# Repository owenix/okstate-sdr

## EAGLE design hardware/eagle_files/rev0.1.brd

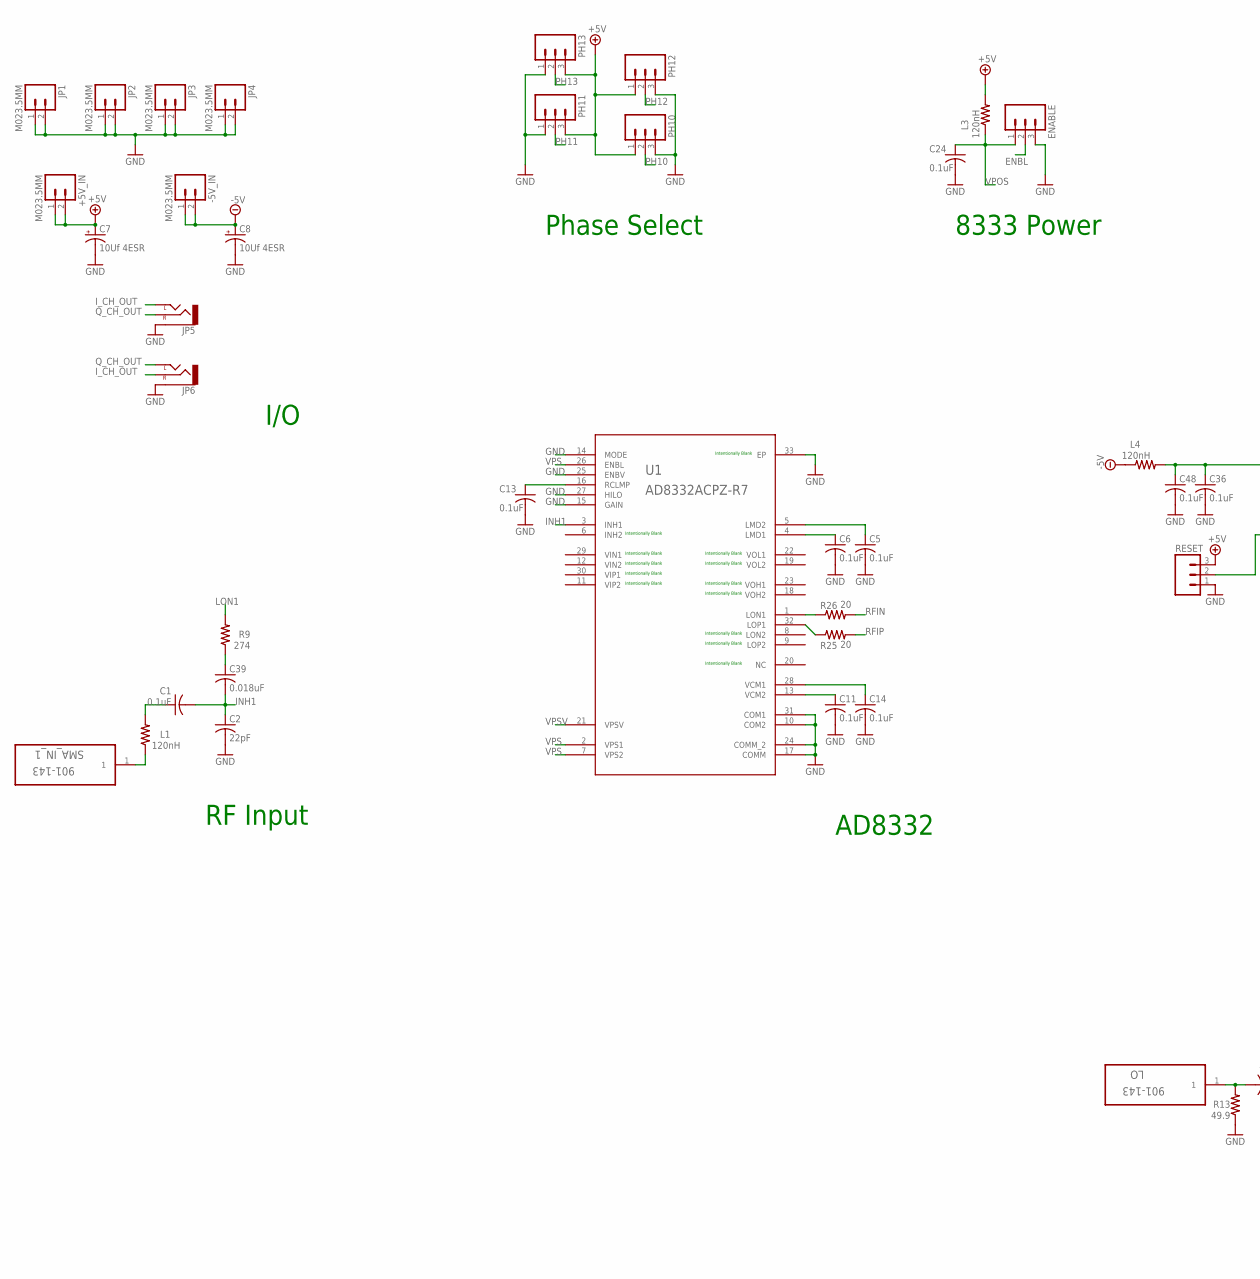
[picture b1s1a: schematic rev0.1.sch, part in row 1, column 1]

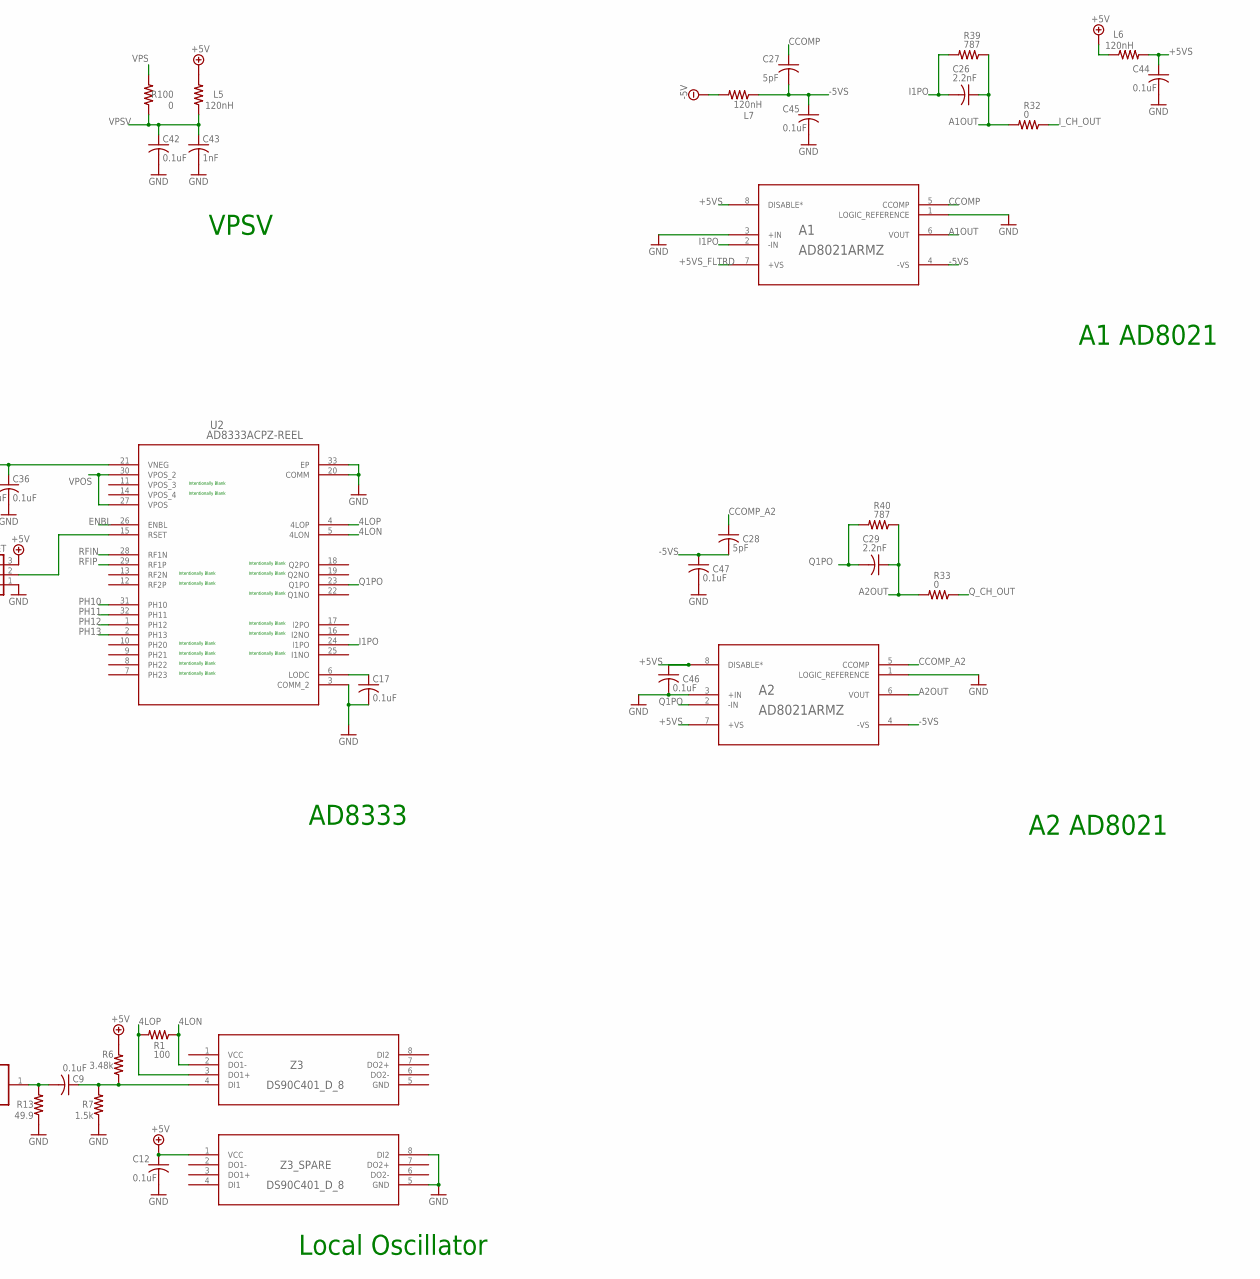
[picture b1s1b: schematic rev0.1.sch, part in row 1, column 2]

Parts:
+5V_IN: M023.5MM; SCREWTERMINAL-3.5MM-2
-5V_IN: M023.5MM; SCREWTERMINAL-3.5MM-2
A1, A2: AD8021ARMZ; RM_8
C1, C5, C6, C9, C11, C12, C13, C14, C17, C24, C36, C42, C44, C45, C46, C47, C48: 0.1uF; C1206
C2: 22pF; C1206
C7, C8: 10Uf 4ESR; CT3216
C26, C29: 2.2nF; C1206
C27, C28: 5pF; C1206
C39: 0.018uF; C1206
C43: 1nF; C1206
ENABLE: M03PTH; 1X03
JP1, JP2, JP3, JP4: M023.5MM; SCREWTERMINAL-3.5MM-2
JP5, JP6: AUDIO-JACKPTH; AUDIO-JACK
L1, L3, L4, L5, L6, L7: 120nH; R0603
LO: 901-143; AMPHENOL_901-143
PH10, PH11, PH12, PH13: M03PTH; 1X03
R1: 100; R1206
R6: 3.48k; R1206
R7: 1.5k; R1206
R9: 274; R1206
R13: 49.9; R1206
R25, R26: 20; R1206
R32, R33, R100: 0; R1206
R39, R40: 787; R1206
RESET: M03PTH; 1X03
SMA_IN_1: 901-143; AMPHENOL_901-143
U1: AD8332ACPZ-R7; CP_32_2
U2: AD8333ACPZ-REEL; CP_32_2
Z3, Z3_SPARE: DS90C401_D_8; M08A

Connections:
4LON: R1.1, U2.5 (4LON), Z3.2 (DO1-)
4LOP: R1.2, U2.4 (4LOP), Z3.3 (DO1+)
+5V: +5V_IN.1, +5V_IN.2, C7.- (+), C12.1, L3.2, L5.2, L6.1, PH10.1, PH11.3, PH12.1, PH13.3, R6.2, RESET.3, Z3_SPARE.1 (VCC)
+5VS: A1.8 (DISABLE*), A2.7 (+VS), A2.8 (DISABLE*), C44.1, C46.1, L6.2
+5VS_FLTRD: A1.7 (+VS)
-5V: -5V_IN.1, -5V_IN.2, C8.- (+), L4.1, L7.2
-5VS: A1.4 (-VS), A2.4 (-VS), C27.2, C28.2, C45.1, C47.1, L7.1
A1OUT: A1.6 (VOUT), C26.1, R32.2, R39.1
A2OUT: A2.6 (VOUT), C29.1, R33.2, R40.1
CCOMP: A1.5 (CCOMP), C27.1
CCOMP_A2: A2.5 (CCOMP), C28.1
ENBL: ENABLE.2, U2.26 (ENBL)
GND: A1.1 (LOGIC_REFERENCE), A1.3 (+IN), A2.1 (LOGIC_REFERENCE), A2.3 (+IN), C2.2, C5.2, C6.2, C7.+ (-), C8.+ (-), C11.2, C12.2, C13.2, C14.2, C17.2, C24.2, C36.2, C42.2, C43.2, C44.2, C45.2, C46.2, C47.2, C48.2, ENABLE.3, JP1.1, JP1.2, JP2.1, JP2.2, JP3.1, JP3.2, JP4.1, JP4.2, JP5.SLEEVE, JP6.SLEEVE, PH10.3, PH11.1, PH12.3, PH13.1, R7.1, R13.1, RESET.1, U1.10 (COM2), U1.14 (MODE), U1.15 (GAIN), U1.17 (COMM), U1.24 (COMM_2), U1.25 (ENBV), U1.27 (HILO), U1.31 (COM1), U1.33 (EP), U2.3 (COMM_2), U2.20 (COMM), U2.33 (EP), Z3.5 (GND), Z3_SPARE.5 (GND), Z3_SPARE.8 (DI2)
I1PO: A1.2 (-IN), C26.2, R39.2, U2.24 (I1PO)
INH1: C1.2, C2.1, C39.2, U1.3 (INH1)
I_CH_OUT: JP5.TIP (LEFT), JP6.RING (RIGHT), R32.1
LMD1: C6.1, U1.4 (LMD1)
LMD2: C5.1, U1.5 (LMD2)
LON1: R9.2, R26.1, U1.1 (LON1)
LOP1: R25.1, U1.32 (LOP1)
unnamed: C11.1, U1.13 (VCM2)
unnamed: C14.1, U1.28 (VCM1)
unnamed: C13.1, U1.16 (RCLMP)
unnamed: C1.1, L1.2
unnamed: C9.1, R6.1, R7.2, Z3.4 (DI1)
unnamed: C39.1, R9.1
unnamed: L1.1, SMA_IN_1.1
unnamed: C9.2, LO.1, R13.2
unnamed: C36.1, C48.1, L4.2, U2.21 (VNEG)
unnamed: C17.1, U2.6 (LODC)
unnamed: RESET.2, U2.15 (RSET)
PH10: PH10.2, U2.31 (PH10)
PH11: PH11.2, U2.32 (PH11)
PH12: PH12.2, U2.1 (PH12)
PH13: PH13.2, U2.2 (PH13)
Q1PO: A2.2 (-IN), C29.2, R40.2, U2.23 (Q1PO)
Q_CH_OUT: JP5.RING (RIGHT), JP6.TIP (LEFT), R33.1
RFIN: R26.2, U2.28 (RF1N)
RFIP: R25.2, U2.29 (RF1P)
VCC: Z3.1 (VCC)
VPOS: C24.1, ENABLE.1, L3.1, U2.27 (VPOS), U2.30 (VPOS_2)
VPS: R100.2, U1.2 (VPS1), U1.7 (VPS2), U1.26 (ENBL)
VPSV: C42.1, C43.1, L5.1, R100.1, U1.21 (VPSV)

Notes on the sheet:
Intentionally Blank
RF Input
VPSV
AD8332
Local Oscillator
Phase Select
8333 Power
AD8333
A1 AD8021
A2 AD8021
I/O

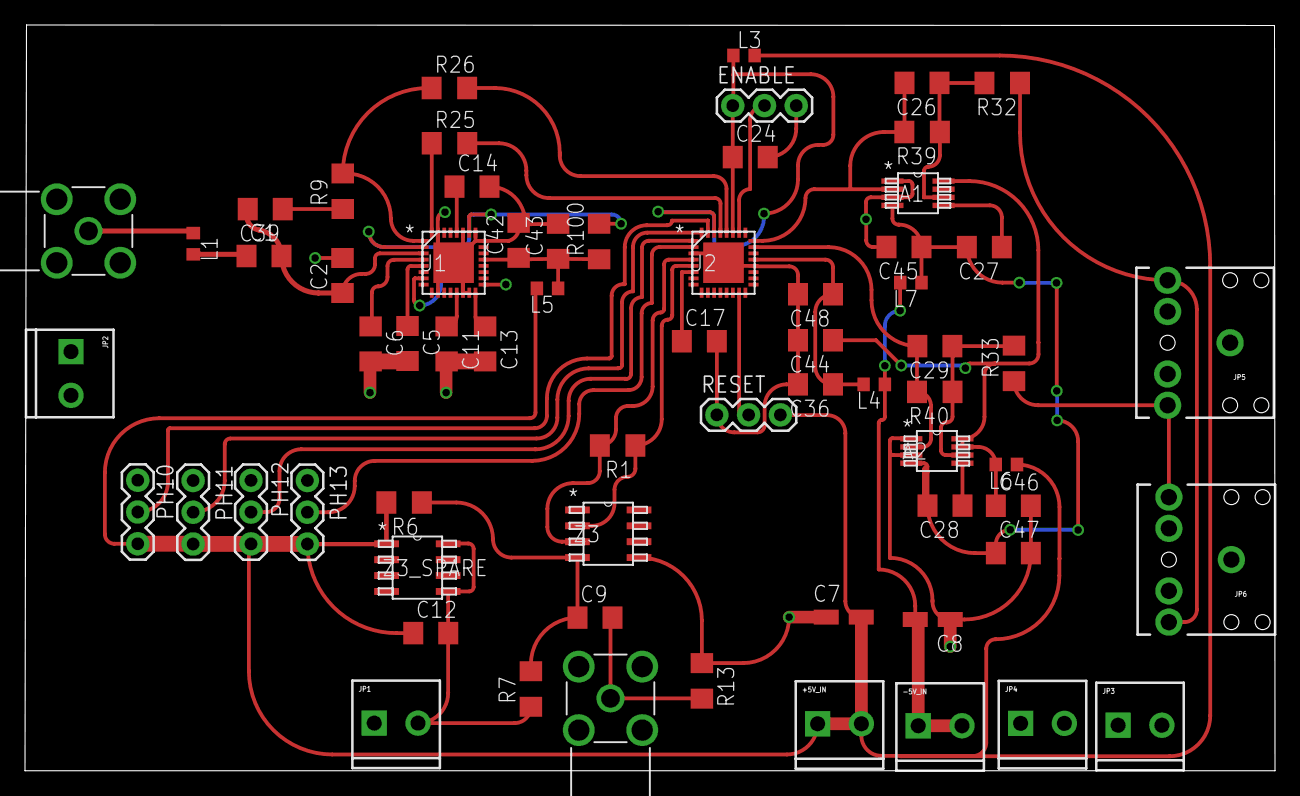
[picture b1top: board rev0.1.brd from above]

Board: 2 copper layers, 100.0 x 59.7 mm, 66 parts (0 on the bottom side), 41 nets.

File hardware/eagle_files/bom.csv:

Qty,Value,Device,Package,Parts,Description,BASE_PN,COMPTYPE,MANUFACTURER_PART_NUMBER,MF,MPN,OC_FARNELL,OC_NEWARK,PACKAGE,PARTNUMBER,SUPPLIER,SYMBOL,TYPE,VENDOR,VERSION
17,0.1uF,C-USC1206,C1206,"C1, C3, C4, C5, C6, C9, C11, C13, C14, C17, C36, C42, C44, C45, C46, C47, C48","CAPACITOR, American symbol",,,,,,,,,,,,,,
6,120nH,R-US_R0603,R0603,"L1, L3, L4, L5, L6, L7","RESISTOR, American symbol",,,,,,,,,,,,,,
6,22-23-2031,22-23-2031,22-23-2031,"ENABLE, PH10, PH11, PH12, PH13, RST",".100"" (2.54mm) Center Header - 3 Pin",,,,MOLEX,22-23-2031,1462950,30C0862,,,,,,,
6,M023.5MM,M023.5MM,SCREWTERMINAL-3.5MM-2,"+5V_IN, -5V_IN, JP1, JP2, JP3, JP4","Standard 2-pin 0.1"" header. Use with",,,,,,,,,,,,,,
3,0,R-US_R1206,R1206,"R32, R33, R100","RESISTOR, American symbol",,,,,,,,,,,,,,
2,,AUDIO-JACKPTH,AUDIO-JACK,"JP5, JP6",3.5mm Audio Jack,,,,,,,,,,,,,,
2,10Uf 4ESR,CPOL-USCT3216,CT3216,"C7, C8","POLARIZED CAPACITOR, American symbol",,,,,,,,,,,,,,
2,2.2nF,C-USC1206,C1206,"C26, C29","CAPACITOR, American symbol",,,,,,,,,,,,,,
2,20,R-US_R1206,R1206,"R25, R26","RESISTOR, American symbol",,,,,,,,,,,,,,
2,5pF,C-USC1206,C1206,"C27, C28","CAPACITOR, American symbol",,,,,,,,,,,,,,
2,787,R-US_R1206,R1206,"R39, R40","RESISTOR, American symbol",,,,,,,,,,,,,,
2,901-143,901-143,AMPHENOL_901-143,"LO, SMA_IN_1","RF/COAXIAL, SMA JACK, R/A, 50OHM, THD",,,,,901-143,1461631,51F3841,"RF/COAXIAL, SMA JACK, R/A, 50OHM, THD ",,Amphenol,,,,
2,AD8021ARMZ,AD8021ARMZ,RM_8,"A1, A2",,,,AD8021ARMZ,,,,,,,,,,Vendor,
2,DS90C401_D_8,DS90C401_D_8,M08A,"Z3, Z3_SPARE",,DS90C401,Interface,,,,,,,DS90C401M,,NameDS90C401M,DS90C401M,NationalSemiconductor,05/02/2007
1,0.018uF,C-USC1206,C1206,C39,"CAPACITOR, American symbol",,,,,,,,,,,,,,
1,1.5k,R-US_R1206,R1206,R7,"RESISTOR, American symbol",,,,,,,,,,,,,,
1,100,R-US_R1206,R1206,R1,"RESISTOR, American symbol",,,,,,,,,,,,,,
1,1nF,C-USC1206,C1206,C43,"CAPACITOR, American symbol",,,,,,,,,,,,,,
1,22pF,C-USC1206,C1206,C2,"CAPACITOR, American symbol",,,,,,,,,,,,,,
1,274,R-US_R0603,R0603,R9,"RESISTOR, American symbol",,,,,,,,,,,,,,
1,3.48k,R-US_R1206,R1206,R6,"RESISTOR, American symbol",,,,,,,,,,,,,,
1,49.9,R-US_R1206,R1206,R13,"RESISTOR, American symbol",,,,,,,,,,,,,,
1,AD8332ACPZ-R7,AD8332ACPZ-R7,CP_32_2,U1,,,,AD8332ACPZ-R7,,,,,,,,,,Vendor,
1,AD8333ACPZ-REEL,AD8333ACPZ-REEL,CP_32_2,U2,,,,,,,,,,,,,,,

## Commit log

2014-12-16 added proposal document
2014-12-17 added demod bom and schema from Analog Devices reference
2014-12-27 Created eagle footprints for parts not in database
2014-12-27 Pushed incomplete schematic
2014-12-30 Completed Preamplifier stage of the design
2015-01-03 Replaced UL script files with Eagle lbr files. Added ds90C401
2015-01-03 Added Local Osc
2015-01-05 Added AD8333
2015-01-05 Added AD8021 x 2
2015-01-09 revision 0.1 complete: Included in this upload is an html version of the BOM
2015-01-09 Added tantalum caps to source input
2015-01-09 Added CSV BOM
2015-01-10 Expanded reference materials
2015-01-23 Issue 7 fixed: Changed C3 to C12
2015-01-23 Issue 12 fixed: Changed C4 to C24
2015-01-23 Issue 19 fixed: Added all EP to ground plane.
2015-02-25 All traces routed
2015-03-05 PCB Routing and CAM
2015-03-05 Revert "Merge branch 'testing'"
    This reverts commit 1c03a4f08a7e645ded5963908e2cd111b4f573d5, reversing
    changes made to 3c7fc9d85ec06c8d7403cfe22418ea7a3d002a55.
2015-04-25 Migrating wiki contents from Google Code

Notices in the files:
parts and their libraries:
SparkFun-Connectors: Licensing: Creative Commons ShareAlike 4.0 International - https://creativecommons.org/licenses/by-sa/4.0
